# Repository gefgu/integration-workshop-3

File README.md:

# TedTronics - Team #2

**TedTronics: Tutor Educacional para Eletrônica**

TedTronics is the team project for Integration Workshop 3 at UTFPR-CT.

It is an interactive electronics workbench for Fundamental II students: they build a real circuit out of Lego-like component capsules on a connection table, press **Energizar**, and watch it actually work while a guided tutor walks them through each step.

## Documentation

Project documentation (blog, project description, requirements, budget, risk analysis, guided modules, and tasks/Gantt) has moved to Notion:

📄 [Project Notion](https://app.notion.com/p/fdd9670c116e82209954010e6b830a37)

## Software (D3): teacher website, teacher app, server and bench

| Part | Folder | What it does |
|---|---|---|
| Server API | `graph_validator/` | FastAPI + SQLite (Alembic): teacher accounts, lessons, modules, classes, students (each with a unique `uid`), bench sync, dashboard, and the graph validator. |
| Teacher website | `teacher_authoring_app/` (`index.html`) | Phone-first React site: sign-up/login, lesson editor, modules, classes, students (with their unique ID), performance dashboard. |
| Teacher app | `teacher_mobile_app/` | Expo / React Native: login, classes and students, connect to a bench (Bluetooth or simulator), pick the class and the student who will use the bench, send a module, sync progress, offline queue. |
| Bench | `bench/service/` + `teacher_authoring_app/bench.html` | Bench service (local storage, protocol, local validation) and the 7" screen: the student the teacher picked enters, guided lesson, challenge, score and top-3 ranking. |
| Protocol | `protocol/bench.ts`, `docs/bench-protocol.md` | App ⇄ bench messages, framed for BLE; the simulator carries the same frames over WebSocket. |

### Setup

1. `cd graph_validator && python -m venv .venv`, then install with `.venv/bin/pip install -e ".[dev]" -e ../bench/service` (Windows: `.venv\Scripts\pip ...`).
2. `cd teacher_authoring_app && npm install`
3. Start everything: `./run.sh` (Linux/macOS/Git Bash) or `powershell -ExecutionPolicy Bypass -File run.ps1` (Windows). This applies the migrations and starts:
   - API on `http://<pc>:8000`
   - bench service on `http://<pc>:8765` (demo mode on)
   - website on `http://<pc>:5173`, bench screen on `http://<pc>:5173/bench.html`
4. Teacher app: `cd teacher_mobile_app && npm install && npx expo start`. In Expo Go only the **Simulador** link works. Bluetooth needs a development build (`npx expo run:android`). On the login screen, use the PC's IP: `http://<pc>:8000`.

The demo teacher created by the migration is `professor@tedtronics.local` / `tedtronics`. New teachers sign up on the website. Data lives in `graph_validator/tedtronics.sqlite3` and `bench/service/bench.sqlite3`; both are git-ignored. `TEDTRONICS_DATABASE_URL` points the API to another file. `TEDTRONICS_BENCH_SECRET` must be the same on the API and on the bench: it signs the session that unlocks the bench.

### End-to-end demo

1. On the website: sign up → create lessons (one guided, one challenge) → **Módulos**: create a module with them and tick the class → **Alunos**: register students (each gets a unique ID).
2. In the app: log in → **Bancada** → **Simulador** → `<pc>:8765` → **Levar aula** (class → student who will use the bench → module). Without the phone, the bench screen's "Modo demonstração" loads a curriculum module with demo students.
3. On `bench.html`: the screen greets the chosen student → **Entrar** → do the lesson → leave halfway and come back: it resumes at the same step → the challenge shows the score and the top 3. To hand the bench to another student, send the module again for them from the app (the bench switches students; the previous one's progress is kept).
4. In the app: **Sincronizar progresso** (with no internet, the data waits on the phone and goes up later) → the website's **Painel** shows progress, score and time.

### Tests

- `graph_validator`: `.venv/bin/python -m pytest`
- `bench/service`: `../../graph_validator/.venv/bin/python -m pytest`
- `teacher_authoring_app`: `npm test && npm run typecheck`
- `teacher_mobile_app`: `npm test && npm run typecheck && npx expo lint`

### Tutor voice (Piper TTS)

Saving a lesson also synthesizes everything the tutor says in it (title, instruction, step texts, quiz questions, options and feedback, custom feedback messages) with the offline [Piper](https://github.com/OHF-Voice/piper1-gpl) voice `pt_BR-cadu-medium`, as MP3. Fixed phrases shared by every lesson (default feedback, praise) live in a separate system pack.

1. `cd graph_validator && .venv/bin/pip install -e '.[dev,tts]'`
2. `graph_validator/tools/fetch_voice.sh` downloads the voice (~63 MB) into `graph_validator/voices/` and builds the system pack (~340 phrases, takes several minutes once).

The MP3s are cached by text in `graph_validator/audio/` (both folders are git-ignored; override with `TEDTRONICS_AUDIO_DIR` and `TEDTRONICS_PIPER_VOICE`), so re-saving only synthesizes changed phrases. "Exportar" downloads a `.zip` with `lesson.json` and `audio/*.mp3`; `GET /tts/system.zip` has the system pack. Without the `tts` extra or the voice, lessons still save, just without audio. Rebuild the system pack (`.venv/bin/python -m graph_validator.tts system`) after changing default messages in `feedback.py`.

## Team

- Gabriel Martines
- Gustavo Henrique Bruno dos Santos (Project Manager)
- João Vitor Bezerra
- Julia Mariano
- Tainara Novaes

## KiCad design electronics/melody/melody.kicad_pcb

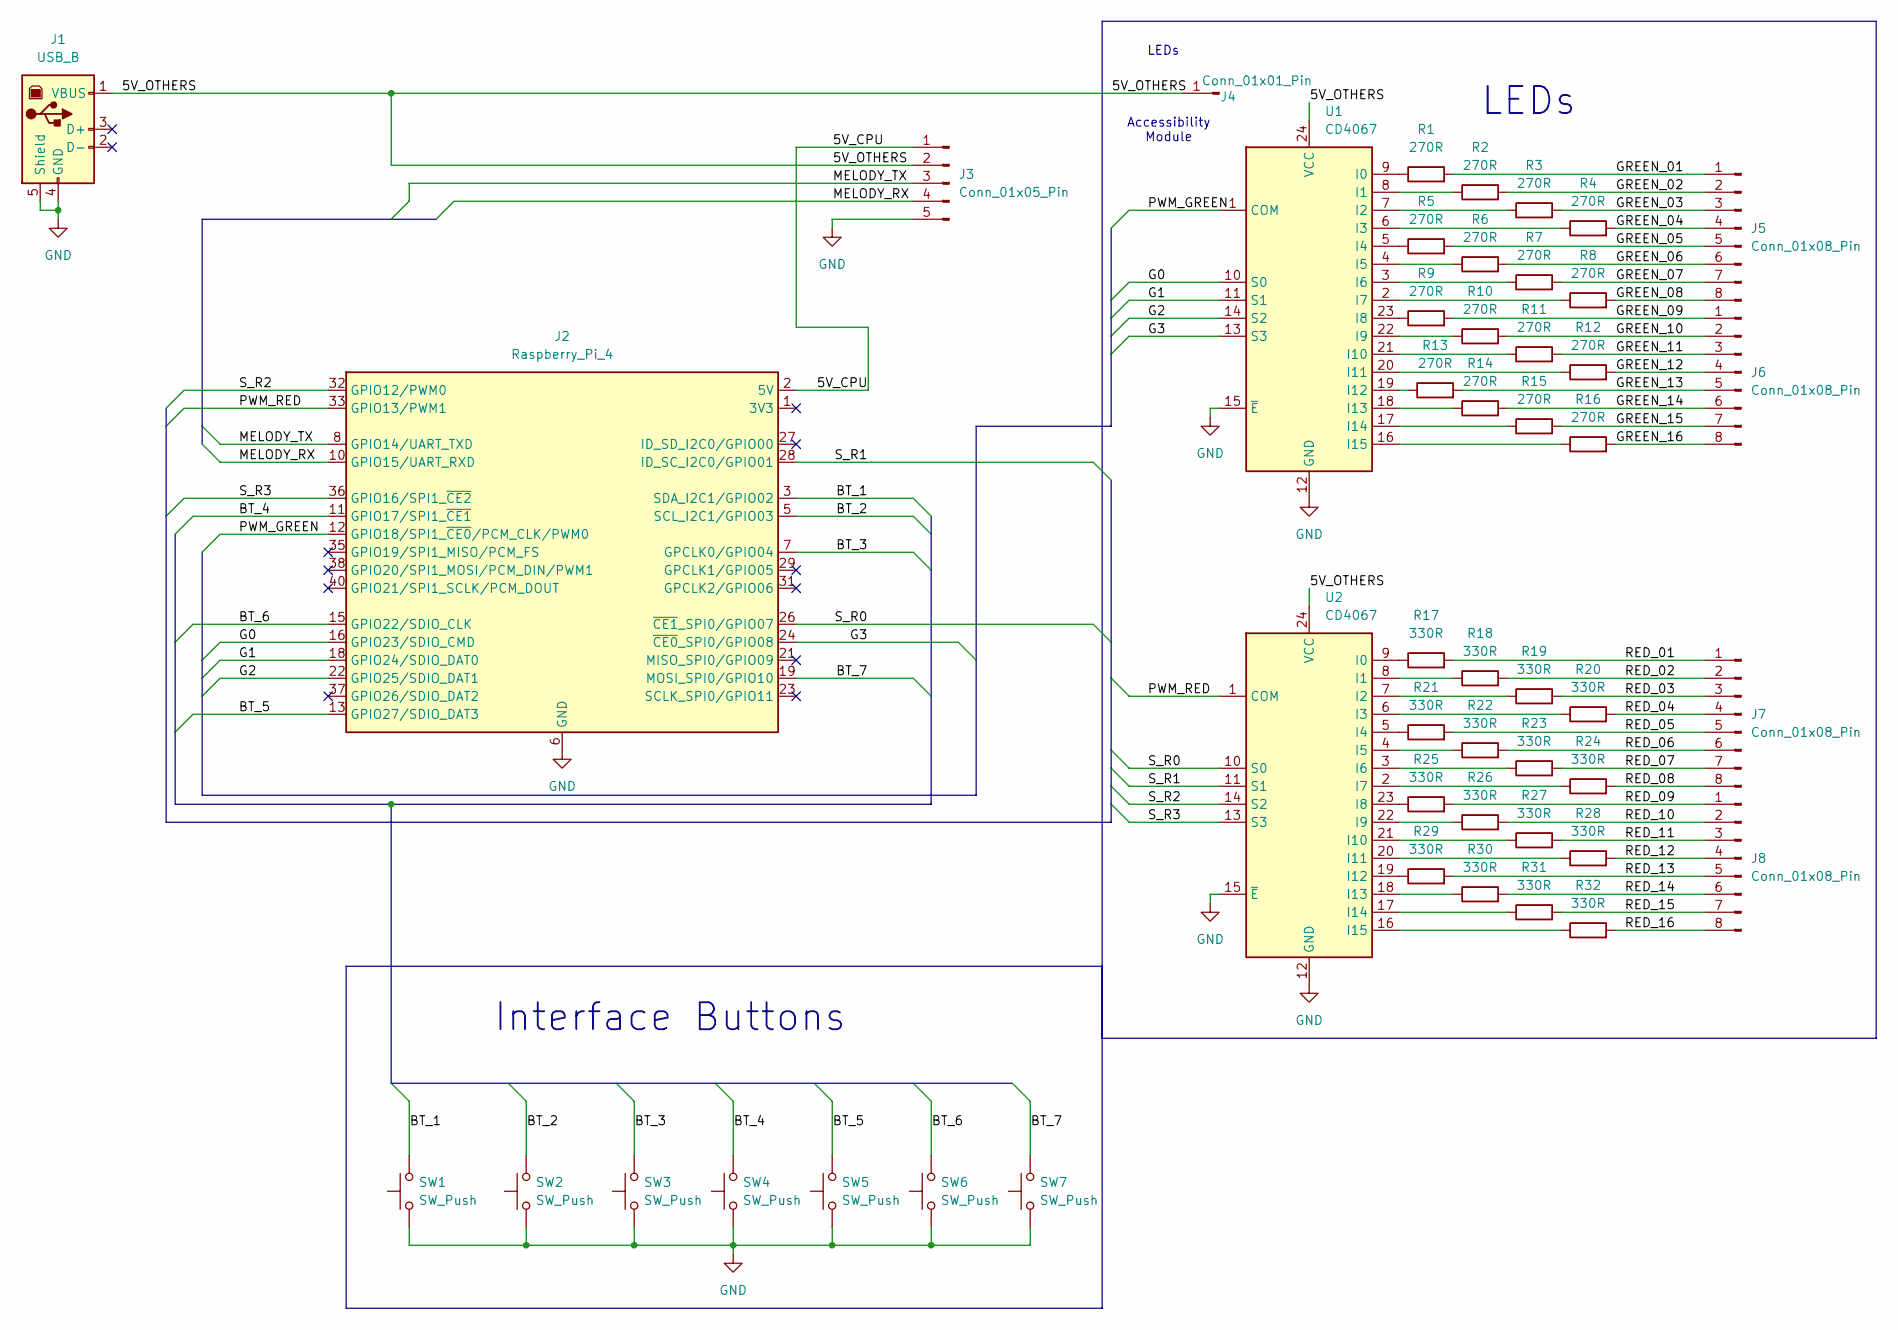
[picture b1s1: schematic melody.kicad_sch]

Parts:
J1: USB_B; USB_B_TE_5787834_Vertical
J2: Raspberry_Pi_4; PinSocket_2x20_P2.54mm_Vertical
J3: Conn_01x05_Pin; PinHeader_1x05_P2.54mm_Vertical
J4: Conn_01x01_Pin; PinSocket_1x01_P2.54mm_Vertical
J5, J6, J7, J8: Conn_01x08_Pin; PinHeader_1x08_P2.54mm_Vertical
R1, R2, R3, R4, R5, R6, R7, R8, R9, R10, R11, R12, R13, R14, R15, R16: 270R; R_Axial_DIN0204_L3.6mm_D1.6mm_P7.62mm_Horizontal
R17, R18, R19, R20, R21, R22, R23, R24, R25, R26, R27, R28, R29, R30, R31, R32: 330R; R_Axial_DIN0204_L3.6mm_D1.6mm_P7.62mm_Horizontal
SW1, SW2, SW3, SW4, SW5, SW6, SW7: SW_Push; PinHeader_1x02_P2.54mm_Vertical
U1, U2: CD4067; DIP-24_W15.24mm_LongPads

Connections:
/5V_CPU: J2.2 (5V), J2.4 (5V), J3.1
/5V_OTHERS: J1.1 (VBUS), J3.2, J4.1, U1.24 (VCC), U2.24 (VCC)
/BT_1: J2.3 (SDA_I2C1/GPIO02), SW1.2
/BT_2: J2.5 (SCL_I2C1/GPIO03), SW2.2
/BT_3: J2.7 (GPCLK0/GPIO04), SW3.2
/BT_4: J2.11 (GPIO17/SPI1_~CE1), SW4.2
/BT_5: J2.13 (GPIO27/SDIO_DAT3), SW5.2
/BT_6: J2.15 (GPIO22/SDIO_CLK), SW6.2
/BT_7: J2.19 (MOSI_SPI0/GPIO10), SW7.2
/G0: J2.16 (GPIO23/SDIO_CMD), U1.10 (S0)
/G1: J2.18 (GPIO24/SDIO_DAT0), U1.11 (S1)
/G2: J2.22 (GPIO25/SDIO_DAT1), U1.14 (S2)
/G3: J2.24 (~CE0_SPI0/GPIO08), U1.13 (S3)
/GREEN_01: J5.1, R1.2
/GREEN_02: J5.2, R2.2
/GREEN_03: J5.3, R3.2
/GREEN_04: J5.4, R4.2
/GREEN_05: J5.5, R5.2
/GREEN_06: J5.6, R6.2
/GREEN_07: J5.7, R7.2
/GREEN_08: J5.8, R8.2
/GREEN_09: J6.1, R9.2
/GREEN_10: J6.2, R10.2
/GREEN_11: J6.3, R11.2
/GREEN_12: J6.4, R12.2
/GREEN_13: J6.5, R13.2
/GREEN_14: J6.6, R14.2
/GREEN_15: J6.7, R15.2
/GREEN_16: J6.8, R16.2
/MELODY_RX: J2.10 (GPIO15/UART_RXD), J3.4
/MELODY_TX: J2.8 (GPIO14/UART_TXD), J3.3
/PWM_GREEN: J2.12 (GPIO18/SPI1_~CE0/PCM_CLK/PWM0), U1.1 (COM)
/PWM_RED: J2.33 (GPIO13/PWM1), U2.1 (COM)
/R0: J2.26 (~CE1_SPI0/GPIO07), U2.10 (S0)
/R1: J2.28 (ID_SC_I2C0/GPIO01), U2.11 (S1)
/R2: J2.32 (GPIO12/PWM0), U2.14 (S2)
/R3: J2.36 (GPIO16/SPI1_~CE2), U2.13 (S3)
/RED_01: J7.1, R17.2
/RED_02: J7.2, R18.2
/RED_03: J7.3, R19.2
/RED_04: J7.4, R20.2
/RED_05: J7.5, R21.2
/RED_06: J7.6, R22.2
/RED_07: J7.7, R23.2
/RED_08: J7.8, R24.2
/RED_09: J8.1, R25.2
/RED_10: J8.2, R26.2
/RED_11: J8.3, R27.2
/RED_12: J8.4, R28.2
/RED_13: J8.5, R29.2
/RED_14: J8.6, R30.2
/RED_15: J8.7, R31.2
/RED_16: J8.8, R32.2
GND: J1.4 (GND), J1.5 (Shield), J2.6 (GND), J2.9 (GND), J2.14 (GND), J2.20 (GND), J2.25 (GND), J2.30 (GND), J2.34 (GND), J2.39 (GND), J3.5, SW1.1, SW2.1, SW3.1, SW4.1, SW5.1, SW6.1, SW7.1, U1.12 (GND), U1.15 (~E), U2.12 (GND), U2.15 (~E)
unnamed: R1.1, U1.9 (I0)
unnamed: R2.1, U1.8 (I1)
unnamed: R3.1, U1.7 (I2)
unnamed: R4.1, U1.6 (I3)
unnamed: R5.1, U1.5 (I4)
unnamed: R6.1, U1.4 (I5)
unnamed: R7.1, U1.3 (I6)
unnamed: R8.1, U1.2 (I7)
unnamed: R9.1, U1.23 (I8)
unnamed: R10.1, U1.22 (I9)
unnamed: R11.1, U1.21 (I10)
unnamed: R12.1, U1.20 (I11)
unnamed: R13.1, U1.19 (I12)
unnamed: R14.1, U1.18 (I13)
unnamed: R15.1, U1.17 (I14)
unnamed: R16.1, U1.16 (I15)
unnamed: R17.1, U2.9 (I0)
unnamed: R18.1, U2.8 (I1)
unnamed: R19.1, U2.7 (I2)
unnamed: R20.1, U2.6 (I3)
unnamed: R21.1, U2.5 (I4)
unnamed: R22.1, U2.4 (I5)
unnamed: R23.1, U2.3 (I6)
unnamed: R24.1, U2.2 (I7)
unnamed: R25.1, U2.23 (I8)
unnamed: R26.1, U2.22 (I9)
unnamed: R27.1, U2.21 (I10)
unnamed: R28.1, U2.20 (I11)
unnamed: R29.1, U2.19 (I12)
unnamed: R30.1, U2.18 (I13)
unnamed: R31.1, U2.17 (I14)
unnamed: R32.1, U2.16 (I15)

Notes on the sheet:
Interface Buttons
LEDs
Accessibility Module

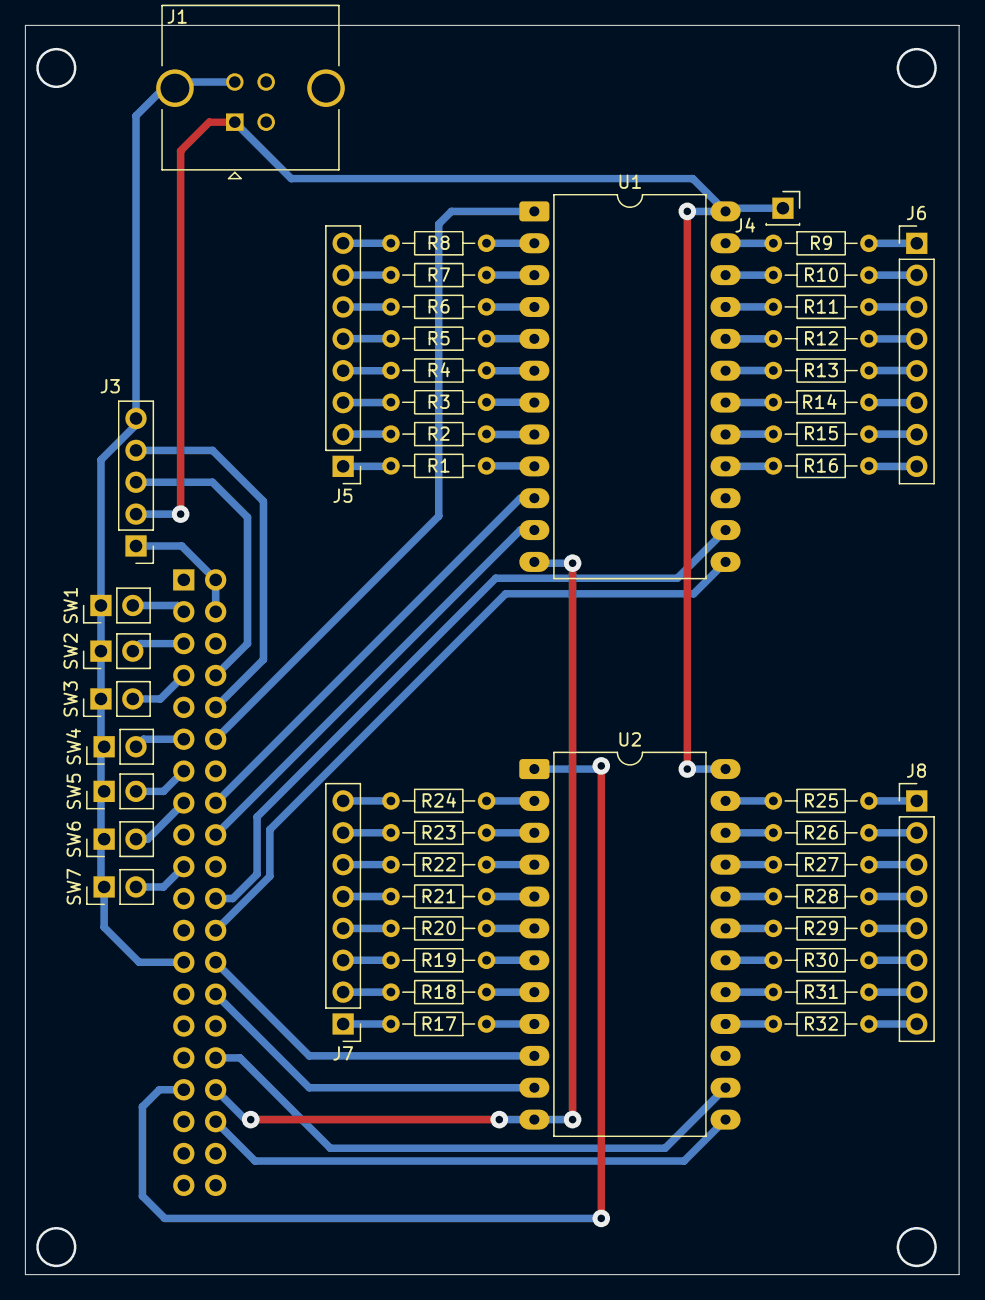
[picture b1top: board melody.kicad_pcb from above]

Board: 2 copper layers, 74.4 x 99.6 mm, 49 parts (1 on the bottom side), 86 nets.

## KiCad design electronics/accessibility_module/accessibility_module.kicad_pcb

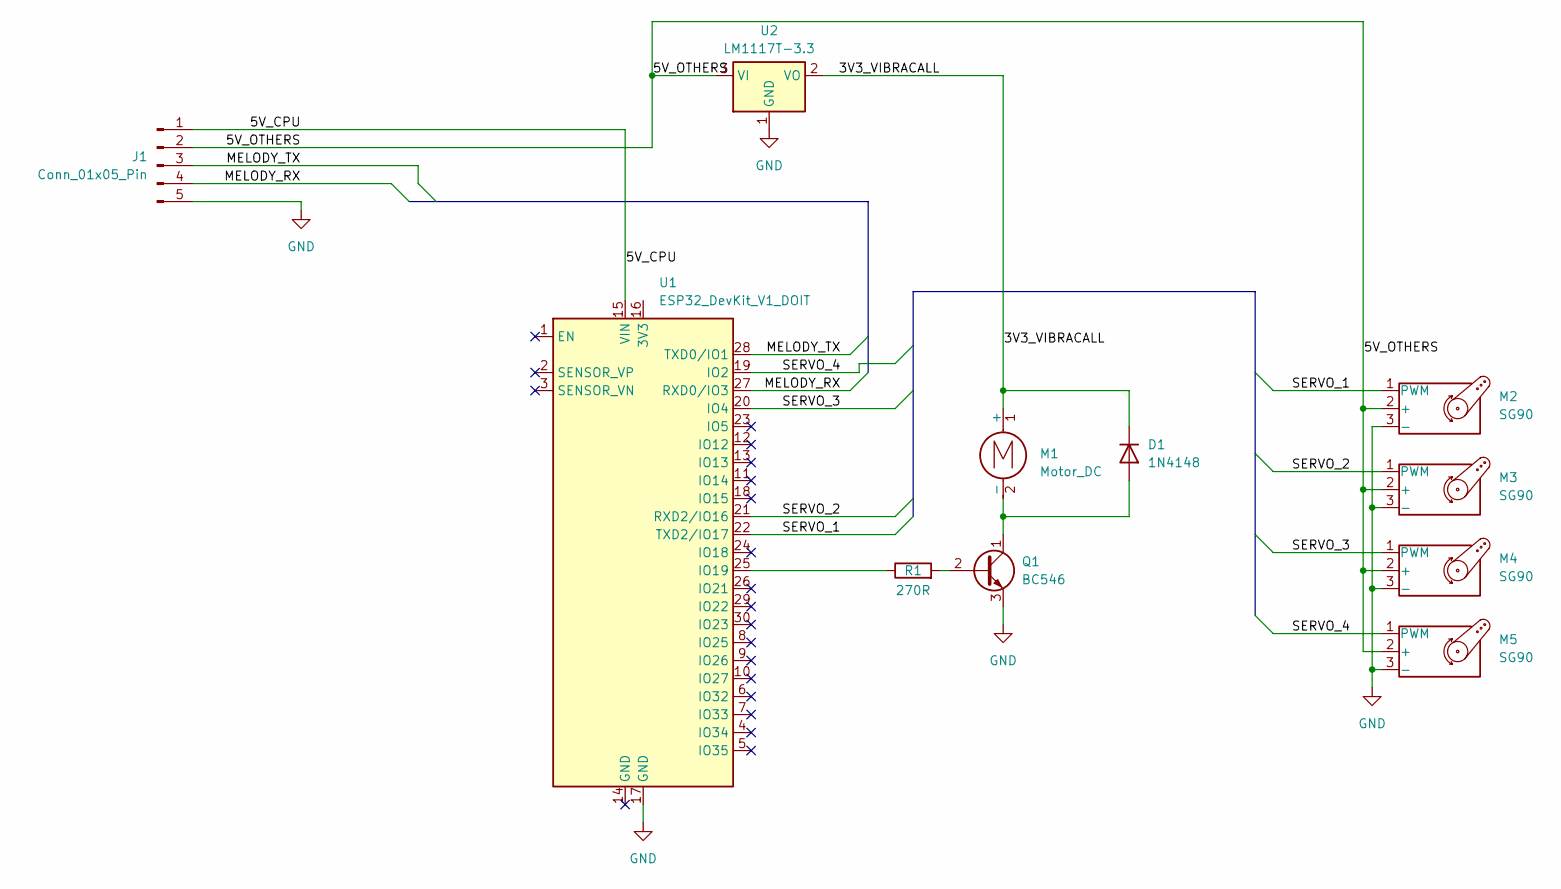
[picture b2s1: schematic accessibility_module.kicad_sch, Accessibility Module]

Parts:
D1: 1N4148; D_DO-35_SOD27_P7.62mm_Horizontal
J1: Conn_01x05_Pin; PinHeader_1x05_P2.54mm_Vertical
M1: Motor_DC; PinHeader_1x02_P2.54mm_Vertical
M2, M3, M4, M5: SG90; PinHeader_1x03_P2.54mm_Vertical
Q1: BC546; TO-92_Inline
R1: 270R; R_Axial_DIN0204_L3.6mm_D1.6mm_P7.62mm_Horizontal
U1: ESP32_DevKit_V1_DOIT; esp32_devkit_v1_doit
U2: LM1117T-3.3; TO-220-3_Vertical

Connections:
/3V3_VIBRACALL: D1.1 (K), M1.1 (+), U2.2 (VO)
/5V_CPU: J1.1, U1.15 (VIN)
/5V_OTHERS: J1.2, M2.2 (+), M3.2 (+), M4.2 (+), M5.2 (+), U2.3 (VI)
/MELODY_RX: J1.4, U1.27 (RXD0/IO3)
/MELODY_TX: J1.3, U1.28 (TXD0/IO1)
/SERVO_1: M2.1 (PWM), U1.22 (TXD2/IO17)
/SERVO_2: M3.1 (PWM), U1.21 (RXD2/IO16)
/SERVO_3: M4.1 (PWM), U1.20 (IO4)
/SERVO_4: M5.1 (PWM), U1.19 (IO2)
GND: J1.5, M2.3 (-), M3.3 (-), M4.3 (-), M5.3 (-), Q1.3 (E), U1.17 (GND), U2.1 (GND)
unnamed: D1.2 (A), M1.2 (-), Q1.1 (C)
unnamed: Q1.2 (B), R1.2
unnamed: R1.1, U1.25 (IO19)

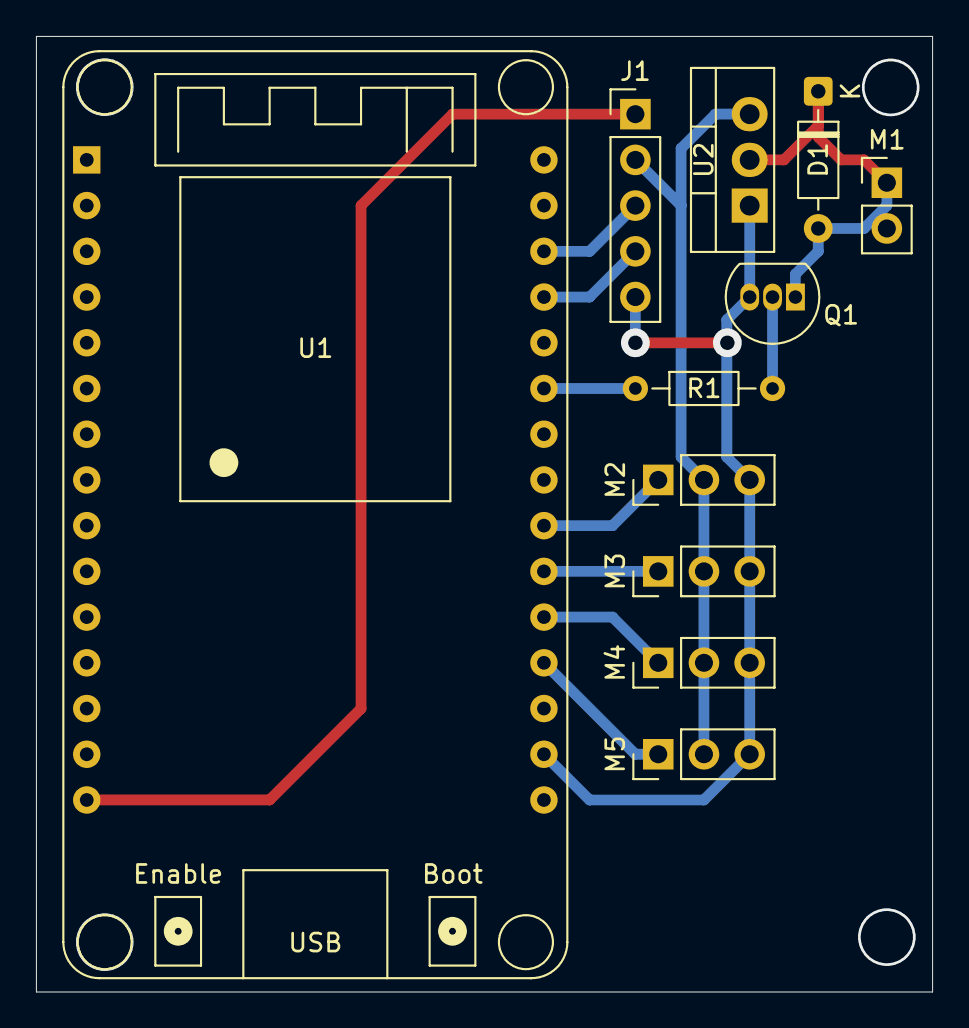
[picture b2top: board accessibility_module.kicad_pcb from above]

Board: 2 copper layers, 49.8 x 53.1 mm, 11 parts (0 on the bottom side), 13 nets.

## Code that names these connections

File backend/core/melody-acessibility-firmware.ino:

#include <ESP32Servo.h>

#define SERVO_1_PIN 2
#define SERVO_2_PIN 4
#define SERVO_3_PIN 16
#define SERVO_4_PIN 17
#define VIBRACALL_PIN 19

#define BUFFER_SIZE 32

Servo servo1;
Servo servo2;
Servo servo3;
Servo servo4;

// Função para definir o duty cycle de um servo específico
void setServoDuty(int servoNum, int duty)
{
    // Garante que o duty cycle está dentro dos limites
    duty = constrain(duty, 0, 100);

    // Mapeia de 0-100% para o valor de pulso do servo (500-2400us é um range comum)
    int pulseWidth = map(duty, 0, 100, 500, 2400);

    // Aplica ao servo correto
    switch (servoNum)
    {
    case 1:
        servo1.writeMicroseconds(pulseWidth);
        break;
    case 2:
        servo2.writeMicroseconds(pulseWidth);
        break;
    case 3:
        servo3.writeMicroseconds(pulseWidth);
        break;
    case 4:
        servo4.writeMicroseconds(pulseWidth);
        break;
    }
}

void setup()
{
    pinMode(VIBRACALL_PIN, OUTPUT);
    Serial.begin(115200);
    servo1.attach(SERVO_1_PIN);
    servo2.attach(SERVO_2_PIN);
    servo3.attach(SERVO_3_PIN);
    servo4.attach(SERVO_4_PIN);

    // Inicia os motores na posicao default
    setServoDuty(SERVO_1_PIN, 0);
    setServoDuty(SERVO_2_PIN, 0);
    setServoDuty(SERVO_3_PIN, 0);
    setServoDuty(SERVO_4_PIN, 0);
}

void loop()
{
    if(Serial.available() > 0){
        char command =Serial.read();
        switch(command){
            case '1':
                setServoDuty(4,50);
                setServoDuty(1,0);
                digitalWrite(VIBRACALL_PIN, HIGH);
                delay(500);
                digitalWrite(VIBRACALL_PIN, LOW);
                break;
            case '2':
                setServoDuty(1,50);
                setServoDuty(2,0);
                digitalWrite(VIBRACALL_PIN, HIGH);
                delay(500);
                digitalWrite(VIBRACALL_PIN, LOW);
                break;
            case '3':
                setServoDuty(2,50);
                setServoDuty(3,0);
                digitalWrite(VIBRACALL_PIN, HIGH);
                delay(500);
                digitalWrite(VIBRACALL_PIN, LOW);
                break;
            case '4':
                setServoDuty(3,50);
                setServoDuty(4,0);
                digitalWrite(VIBRACALL_PIN, HIGH);
                delay(500);
                digitalWrite(VIBRACALL_PIN, LOW);
                break;
            case '5':
                setServoDuty(1,50);
                setServoDuty(2,50);
                setServoDuty(3,50);
                setServoDuty(4,50);
                break;
            case '6':
                digitalWrite(VIBRACALL_PIN,HIGH);
                delay(500);
                digitalWrite(VIBRACALL_PIN,LOW);
                break;
            case '7':
                digitalWrite(VIBRACALL_PIN,HIGH);
                delay(500);
                digitalWrite(VIBRACALL_PIN,LOW);
                delay(50);       
                digitalWrite(VIBRACALL_PIN,HIGH);
                delay(500);
                digitalWrite(VIBRACALL_PIN,LOW);
                break;
        }
    }
}                 
